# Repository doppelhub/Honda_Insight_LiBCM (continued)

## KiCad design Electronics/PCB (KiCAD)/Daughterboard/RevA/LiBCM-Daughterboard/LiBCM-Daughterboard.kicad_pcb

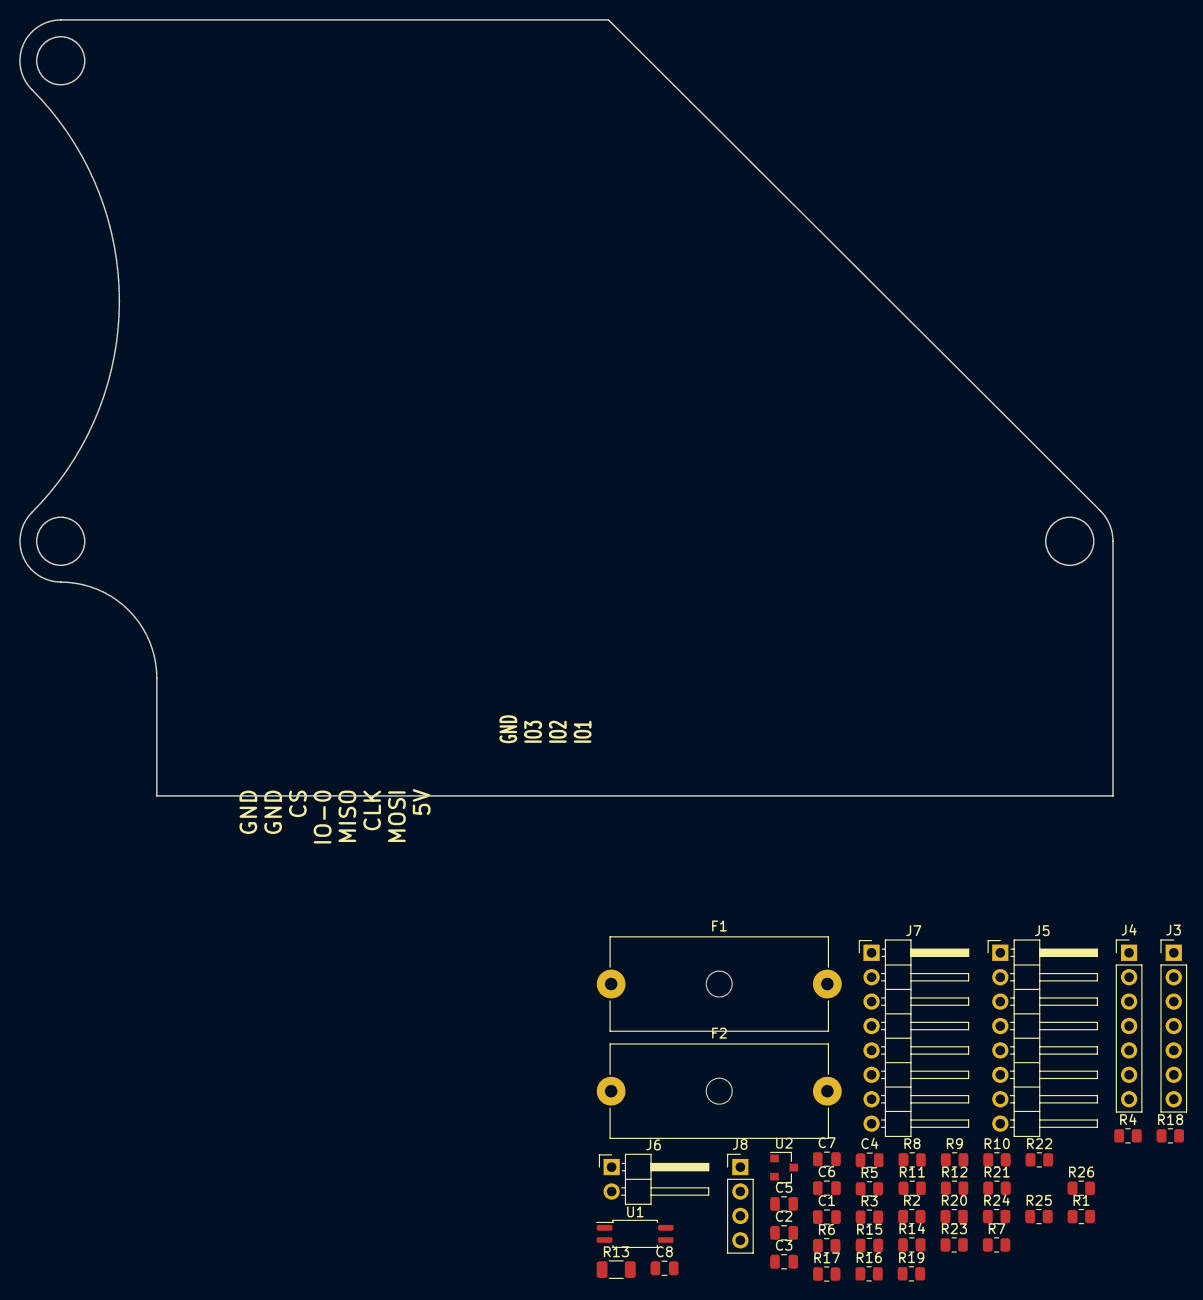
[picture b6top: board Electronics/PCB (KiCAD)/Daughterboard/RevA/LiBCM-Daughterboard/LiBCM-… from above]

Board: 4 copper layers, 113.7 x 80.8 mm, 44 parts (0 on the bottom side), 22 nets, no tracks yet.

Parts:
C1, C2, C3, C4, C5, C7, C8: 100n; C_0805_2012Metric
C6: 1u; C_0805_2012Metric
F1, F2: Fuse; Fuseholder_Cylinder-5x20mm_Schurter_0031_8201_Horizontal_Op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
J3, J4: Conn_01x07; PinHeader_1x07_P2.54mm_Vertical
J5, J7: Conn_01x08; PinHeader_1x08_P2.54mm_Horizontal
J6: Conn_01x02; PinHeader_1x02_P2.54mm_Horizontal
J8: Conn_01x04; PinHeader_1x04_P2.54mm_Vertical
R1, R2, R3, R4: 7k32; R_0805_2012Metric
R5, R6, R7, R18, R24: 10k; R_0805_2012Metric
R8, R9, R23, R25: 768; R_0805_2012Metric
R10, R12: 100; R_0805_2012Metric
R11: 20; R_0805_2012Metric
R13: 5M1; R_1206_3216Metric
R14, R15, R16, R17: 100k; R_0805_2012Metric
R19, R20, R21, R22, R26: DNP; R_0805_2012Metric
U1: APV1121S; SOP-4_4.4x2.6mm_P1.27mm
U2: LM4040DBZ-5; SOT-23

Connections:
+5V: C1.1, C2.1, C3.1, C6.1, J3.1, J4.1, J5.1, J7.1, R1.1, R2.1, R3.1, R4.1
/CHARGER_CURRENT_LIMIT: C8.1, R23.2, R24.1, R25.2, R26.2
/FLASH_CS: J4.7, J5.6, J7.6
/GPIO: J6.1, J8.3, R10.1, R12.1
/GPIO_L1: R10.2, R11.1, R12.2
/GRID_POS_FUSED: F2.1, R14.1, R16.1, R19.1, R21.1
/HVDC_5V_REF: C7.1, R15.2, R17.2, R18.1, R20.2, R22.2, R23.1, R25.1, R26.1, U2.1
/MIMA_CS: J5.5, J7.5
/MISO: J3.4, J4.5, J5.4, J7.4
/MOSI: J3.5, J4.6, J5.3, J7.3
/Q1_GATE: R13.1, U1.4
/SCK: J3.6, J4.4, J5.2, J7.2
/SWITCH__OR__CAN_CS: J3.3, J8.2, R8.2
/TACH_1: R1.2, R5.1
/TACH_2: R2.2, R6.1
/TACH_3: R3.2, R7.1
/TACH_SUM: C5.1, R5.2, R6.2, R7.2, R9.1
/TACH__OR__CAN_INT: J3.7, J8.1, R9.2
/USER_SWITCH: C4.1, R4.2, R8.1
GND: C1.2, C2.2, C3.2, C4.2, C5.2, C6.2, J3.2, J4.3, J5.7, J5.8, J6.2, J7.7, J7.8, J8.4, U1.2
GNDPWR: C7.2, C8.2, R13.2, R18.2, R24.2, U1.3, U2.2
unnamed: R14.2, R15.1, R16.2, R17.1, R19.2, R20.1, R21.2, R22.1

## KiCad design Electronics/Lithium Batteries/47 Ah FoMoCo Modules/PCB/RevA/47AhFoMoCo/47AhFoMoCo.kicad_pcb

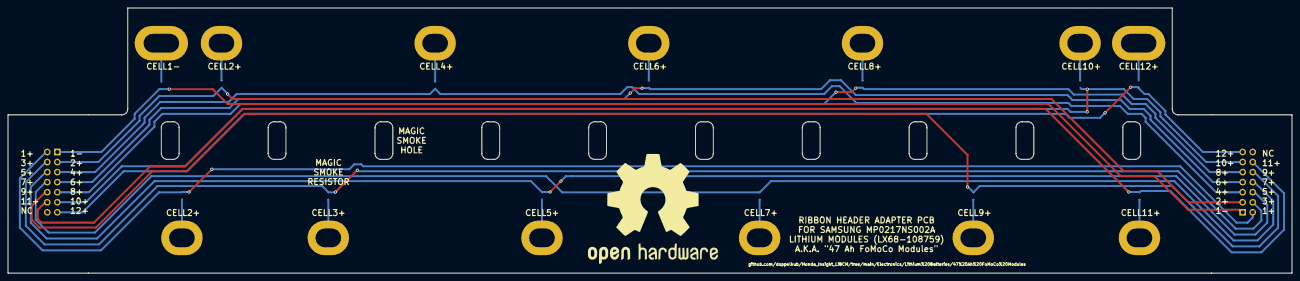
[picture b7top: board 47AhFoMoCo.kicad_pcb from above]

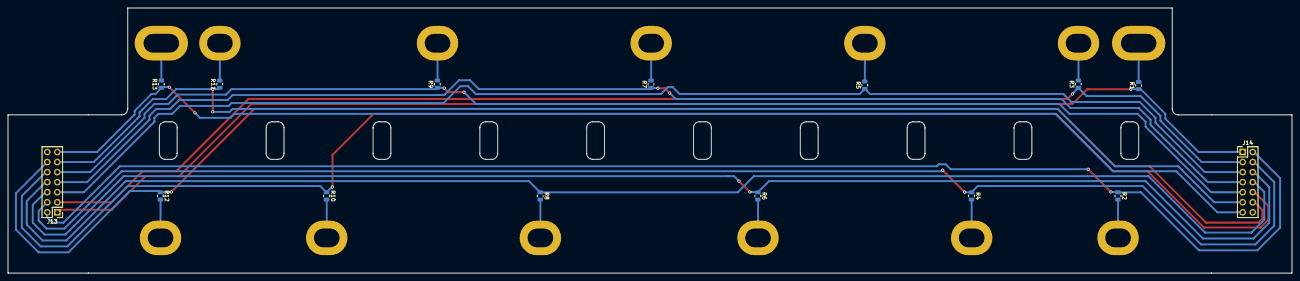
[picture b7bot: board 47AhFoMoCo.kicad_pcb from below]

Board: 2 copper layers, 324.5 x 67.0 mm, 28 parts (15 on the bottom side), 26 nets.

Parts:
J1n1, J12p1: Conn_01x01; BMS Hole_Wide
J1p1, J2p1, J3p1, J4p1, J5p1, J6p1, J7p1, J8p1, J9p1, J10p1, J11p1: Conn_01x01; BMS Hole
J13, J14: Conn_02x07_Odd_Even; PinHeader_2x07_P2.54mm_Vertical
R1, R2, R3, R4, R5, R6, R7, R8, R9, R10, R11, R12, R13: 20; R_0805_2012Metric

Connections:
/CELL01n: J1n1.1, R1.2
/CELL01n_CONN: J13.1, J14.1, R1.1
/CELL01p: J1p1.1, R2.2
/CELL01p_CONN: J13.2, J14.2, R2.1
/CELL02p: J2p1.1, R3.2
/CELL02p_CONN: J13.3, J14.3, R3.1
/CELL03p: J3p1.1, R4.2
/CELL03p_CONN: J13.4, J14.4, R4.1
/CELL04p: J4p1.1, R5.2
/CELL04p_CONN: J13.5, J14.5, R5.1
/CELL05p: J5p1.1, R6.2
/CELL05p_CONN: J13.6, J14.6, R6.1
/CELL06p: J6p1.1, R7.2
/CELL06p_CONN: J13.7, J14.7, R7.1
/CELL07p: J7p1.1, R8.2
/CELL07p_CONN: J13.8, J14.8, R8.1
/CELL08p: J8p1.1, R9.2
/CELL08p_CONN: J13.9, J14.9, R9.1
/CELL09p: J9p1.1, R10.2
/CELL09p_CONN: J13.10, J14.10, R10.1
/CELL10p: J10p1.1, R11.2
/CELL10p_CONN: J13.11, J14.11, R11.1
/CELL11p: J11p1.1, R12.2
/CELL11p_CONN: J13.12, J14.12, R12.1
/CELL12p: J12p1.1, R13.2
/CELL12p_CONN: J13.13, J14.13, R13.1

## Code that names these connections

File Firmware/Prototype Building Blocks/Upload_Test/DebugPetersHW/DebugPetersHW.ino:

//MVP PoC:

/*
* Don't care about:
* -SoC (accumulation)
* -Temperature
* -Fan speed
* -Spoofing ConnE
* -Spoofing Vpin
* -Grid charger
*/

//JTS2do: Move pindefs to a separate header file
#define HW_REVB

#ifdef HW_REVB
  #define PIN_BATTCURRENT A0
  #define PIN_FANOEM_LOW A1
  #define PIN_FANOEM_HI A2
  #define PIN_TEMP_YEL A3
  #define PIN_TEMP_GRN A4
  #define PIN_TEMP_WHT A5
  #define PIN_TEMP_BLU A6
  #define PIN_VPIN_IN A7
  #define PIN_TURNOFFLiBCM A8
  #define PIN_HMI_EN A9
  #define PIN_BATTSCI_DE A10
  #define PIN_BATTSCI_REn A11
  #define PIN_LED1 A12
  #define PIN_LED2 A13
  #define PIN_LED3 A14
  #define PIN_LED4 A15
  
  #define PIN_METSCI_DE 2
  #define PIN_METSCI_REn 3
  #define PIN_VPIN_OUT_PWM 4
  #define PIN_SPI_EXT_CS 5 
  #define PIN_TEMP_EN 6
  #define PIN_CONNE_PWM 7
  #define PIN_GRID_PWM 8
  #define PIN_GRID_SENSE 9
  #define PIN_GRID_EN 10
  #define PIN_FAN_PWM 11
  #define PIN_I_SENSOR_EN 12
  #define PIN_KEY_ON 13
  #define PIN_SPI_CS SS
  #define PIN_GPIO1 48
  #define PIN_USER_SW 49
  
  //Serial3
  #define METSCI_TX 14
  #define METSCI_RX 15
  
  //Serial2
  #define BATTSCI_TX 16
  #define BATTSCI_RX 17
  
  //Serial1
  #define HMI_TX 18
  #define HMI_RX 19
  
  #define DEBUG_SDA 20
  #define DEBUG_CLK 21
#endif

#include <Arduino.h>
#include <stdint.h>
#include "LT_SPI.h"
#include <SPI.h>
#include "LTC68042.h"

struct packetTypes
{
  uint8_t latestE6Packet_assistLevel;
  uint8_t latestB4Packet_engine;
  uint8_t latestB3Packet_engine;
  uint8_t latestE1Packet_SoC;
} METSCI_Packets;

void setup()
{
	//Prevent LiBCM from turning off the 12V->5V DCDC
	pinMode(PIN_TURNOFFLiBCM,OUTPUT);
	digitalWrite(PIN_TURNOFFLiBCM,LOW);
 
	pinMode(PIN_I_SENSOR_EN,OUTPUT);
	digitalWrite(PIN_I_SENSOR_EN,LOW);

	pinMode(PIN_LED1,OUTPUT);
	digitalWrite(PIN_LED1,HIGH);
	pinMode(PIN_LED2,OUTPUT);
	pinMode(PIN_LED3,OUTPUT);
	pinMode(PIN_LED4,OUTPUT);

	pinMode(PIN_CONNE_PWM,OUTPUT);
  analogWrite(PIN_CONNE_PWM,0);
	pinMode(PIN_FAN_PWM,OUTPUT);
	pinMode(PIN_FANOEM_LOW,OUTPUT);
	pinMode(PIN_FANOEM_HI,OUTPUT);
	pinMode(PIN_GRID_EN,OUTPUT);
	pinMode(PIN_VPIN_OUT_PWM,OUTPUT);
  Serial.print("\nPins Set");

  pinMode(PIN_HMI_EN,OUTPUT);
  digitalWrite(PIN_HMI_EN,HIGH); //turn on 4x20 display
  delay(10); //wait for 4x20 to turn on
  Serial.print("\nPass: IO Config");

	analogReference(EXTERNAL); //use 5V AREF pin, which is coupled to filtered VCC

	Serial.begin(115200);	//USB
  Serial.print("\nPass: USB init"); delay(100);
  METSCI_begin();
  Serial.print("\nPass: METSCI init"); delay(100);
  BATTSCI_begin();
  Serial.print("\nPass: BATTSCI init"); delay(100);
  Serial.print("\nPass: one second delay"); delay(1000);
  
  LTC6804_initialize();
  Serial.print("\nPass: LTC6804 init"); delay(100);

  TCCR1B = (TCCR1B & B11111000) | B00000001; // Set onboard fan PWM frequency to 31372 Hz (pins D11 & D12)
  Serial.print("\nPass: set D11/D12 PWM frequency"); delay(100);
    
	Serial.print(F("\n\nPeter's LiBCM HW Debug 2021JUL28a\n\n")); delay(100);
}

//////////////////////////////////////////////////////////////////////////////////////////////////////////////////////////

void loop()
{  
  //Get key position status
  uint8_t keyStatus_now = digitalRead(PIN_KEY_ON);
  static uint8_t keyStatus_previous;
  Serial.print("\nPass(): Key is "); delay(100);
  if(keyStatus_now)
  {
    Serial.print("ON"); delay(100);
  } else {
    Serial.print("OFF"); delay(100);
  }

  //steps to perform when key state changes (on->off, off->on)
  if( keyStatus_now != keyStatus_previous)
  {
    Serial.print(F("\nKey is: ")); delay(100);
    LTC6804_isoSPI_errorCountReset();

    if( keyStatus_now == 0 )
    {
      Serial.print(F("OFF"));
      BATTSCI_disable(); //Must disable BATTSCI when key is off to prevent backdriving MCM
      METSCI_disable();
      digitalWrite(PIN_FANOEM_LOW,LOW);
      digitalWrite(PIN_I_SENSOR_EN,LOW); //disable current sensor & constant 5V load
    } else {
      Serial.print(F("ON"));
      BATTSCI_enable();
      METSCI_enable();
      digitalWrite(PIN_FANOEM_LOW,HIGH);
      digitalWrite(PIN_I_SENSOR_EN,HIGH); //enable current sensor & constant 5V load
    } 
  }
  keyStatus_previous = keyStatus_now;
  
  //---------------------------------------------------------------------------------------

  //Determine whether grid charger is plugged in
  uint8_t gridChargerPowered_now = !(digitalRead(PIN_GRID_SENSE));
  static uint8_t gridChargerPowered_previous;

  //steps to perform when grid charger state changes (plugged in || unplugged)
  if( gridChargerPowered_now != gridChargerPowered_previous)
  {
    Serial.print(F("\nGrid Charger: "));
    if( gridChargerPowered_now == 0 ) //grid charger was just unplugged
    {
      Serial.print(F("Unplugged"));
      analogWrite(PIN_FAN_PWM,0);     //turn onboard fans off
      digitalWrite(PIN_GRID_EN,0);    //turn grid charger off
      Serial.print("\nGrid Charger Disabled");

    } else {                          //grid charger was just plugged in
      Serial.print(F("Plugged In"));
    } 
  }
  gridChargerPowered_previous = gridChargerPowered_now;

  //---------------------------------------------------------------------------------------

  if( (keyStatus_now == 1) || (gridChargerPowered_now == 1) ) //key is on or grid charger plugged in
  {
    digitalWrite(PIN_LED4,HIGH);
    
    LTC6804_startCellVoltageConversion();
    //We don't immediately read the results afterwards because it takes a second to digitize
    //In Coop Task setting we'll need to invoke reading n microseconds after this function is called
    Serial.print("\nPass: LTC6804 Conversion Started"); delay(100);
  
    //---------------------------------------------------------------------------------------

  	//get 64x oversampled current sensor value
    uint16_t ADC_oversampledAccumulator = 0;
    for(int ii=0; ii<64; ii++)  //This takes ~112 us per run (7.2 ms total)
    { 
      ADC_oversampledAccumulator += analogRead(PIN_BATTCURRENT);
    }
    Serial.print("\nPass: Current Sampled"); delay(100);
    
    int16_t ADC_oversampledResult = int16_t( (ADC_oversampledAccumulator >> 6) );
    Serial.print(F("\n\nRaw ADC result is: "));
    Serial.print( String(ADC_oversampledResult) );  
    
  	//convert current sensor result into approximate amperage for MCM & user-display
    //don't use this result for current accumulation... it's not accurate enough
  	int16_t battCurrent_amps = ( (ADC_oversampledResult * 13) >> 6) - 67; //Accurate to within 3.7 amps of actual value
  	Serial.print(F(" counts, which is: "));
    Serial.print( String(battCurrent_amps) );
    Serial.print(F(" amps.  Telling MCM current is: "));
    
    battCurrent_amps = (int16_t)(battCurrent_amps * 0.7); //140% current output required telling MCM 70% of current value
    Serial.print( String(battCurrent_amps) );


    //---------------------------------------------------------------------------------------

  	LTC6804_getCellVoltages(); //individual cell results stored in 'cell_codes' array 
  	
    //sum all 48 cells
  	uint8_t stackVoltage = LTC6804_getStackVoltage();

    //---------------------------------------------------------------------------------------

    if( keyStatus_now ) //key is on
    {
    	//METSCI Decoding
      METSCI_Packets = METSCI_getLatestFrame();
      Serial.print("\nMETSCI E6: " + String(METSCI_Packets.latestE6Packet_assistLevel,HEX) +
                          ", B3: " + String(METSCI_Packets.latestB3Packet_engine,HEX) +
                          ", B4: " + String(METSCI_Packets.latestB4Packet_engine,HEX) +
                          ", E1: " + String(METSCI_Packets.latestE1Packet_SoC,HEX) );

      //---------------------------------------------------------------------------------------  
    	
    	//Send BATTSCI packets to MCM
    	//Need to limit how often this occurs
      BATTSCI_sendFrames(METSCI_Packets, stackVoltage, battCurrent_amps);
    }
    
    delay(100); //forcing buffers to overqueue to verify LiBCM responds correctly
  } else {
    //key is off & grid charger unplugged
    static uint16_t toggleTimer = 0;
    if( ++toggleTimer >= 10000 )
    {
      digitalWrite(PIN_LED4, !digitalRead(PIN_LED4)); //Toggle LED4 (heartbeat)
      toggleTimer=0;   
    }
  }
}

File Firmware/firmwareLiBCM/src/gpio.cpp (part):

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    pinMode(PIN_TURNOFFLiBCM,OUTPUT);
    digitalWrite(PIN_TURNOFFLiBCM,LOW);

    pinMode(PIN_HMI_EN,OUTPUT);
    pinMode(PIN_SENSOR_EN,OUTPUT);
    pinMode(PIN_LED1,OUTPUT);
    pinMode(PIN_LED2,OUTPUT);
    pinMode(PIN_LED3,OUTPUT);
    pinMode(PIN_LED4,OUTPUT);
    analogWrite(PIN_MCME_PWM,0);
    pinMode(PIN_FAN_PWM,OUTPUT);
    pinMode(PIN_FANOEM_LOW,OUTPUT);
    pinMode(PIN_FANOEM_HI,OUTPUT);
    gpio_configureGridChargerPins(); //requires grid charger type, which eeprom_applyBootCriticalConfigOverrides() (called before gpio_begin()) has already resolved
    pinMode(PIN_TEMP_EN,OUTPUT);
    pinMode(PIN_SPI_EXT_CS,OUTPUT);
    digitalWrite(PIN_SPI_EXT_CS,HIGH);

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
//1500W chargers are controlled by a daughterboard, which uses a different pinout than other chargers.
//Grid charger type is a runtime EEPROM value (see eepromAccess.h), so these choose the correct pin at runtime.
uint8_t gpio_pinGridCurrent(void) { return (eeprom_gridChargerType_get() == GRIDCHARGER_TYPE_1500W) ? PIN_GPIO3   : PIN_GRID_PWM; }
uint8_t gpio_pinGridEn(void)      { return (eeprom_gridChargerType_get() == GRIDCHARGER_TYPE_1500W) ? PIN_GRID_PWM : PIN_GRID_EN; }
uint8_t gpio_pinGridVoltage(void) { return PIN_GPIO2; } //only meaningful when grid charger type is 1500W -- other charger types don't support voltage control

void gpio_configureGridChargerPins(void) { pinMode(gpio_pinGridEn(), OUTPUT); }

/////////////////////////////////////////////////////////////////////////////////////////

bool gpio_keyStateNow(void) { return digitalRead(PIN_IGNITION_SENSE); }

/////////////////////////////////////////////////////////////////////////////////////////

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        default: Serial.print(F("\nError: Invalid fan speed"));
    }

    if (fanPWM == 0) { pinMode(PIN_FAN_PWM, INPUT); } //saves power when fan is off
    else             { analogWrite(PIN_FAN_PWM, fanPWM); }
}

/////////////////////////////////////////////////////////////////////////////////////////

//powers OEM current sensor, METSCI/BATTSCI power rail, and constant 5V load
void gpio_turnPowerSensors_on( void) { digitalWrite(PIN_SENSOR_EN, HIGH); }
void gpio_turnPowerSensors_off(void) { digitalWrite(PIN_SENSOR_EN,  LOW); }

/////////////////////////////////////////////////////////////////////////////////////////

void gpio_turnHMI_on( void) { digitalWrite(PIN_HMI_EN, HIGH); }
void gpio_turnHMI_off(void) { digitalWrite(PIN_HMI_EN,  LOW); }
bool gpio_HMIStateNow(void) { return digitalRead(PIN_HMI_EN); }

/////////////////////////////////////////////////////////////////////////////////////////

bool gpio_isGridChargerPluggedInNow(void) { return !(digitalRead(PIN_GRID_SENSE)  ); }
bool gpio_isGridChargerChargingNow(void)  { return   digitalRead(gpio_pinGridEn()); }

/////////////////////////////////////////////////////////////////////////////////////////
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//Buzzer present in RevC+ hardware
void gpio_turnBuzzer_on_highFreq(void)
{
    TCCR5B = (TCCR5B & B11111000) | B00000010; // set F_PWM to  3921.16 Hz //pins D44(GPIO3) & D45(BUZZER) & D46()
    analogWrite(PIN_BUZZER_PWM, 127 );
}

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
void gpio_turnBuzzer_on_lowFreq(void)
{
    TCCR5B = (TCCR5B & B11111000) | B00000011; // set F_PWM to   490.20 Hz //pins D44(GPIO3) & D45(BUZZER) & D46()
    analogWrite(PIN_BUZZER_PWM, 127 );
}

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bool gpio_isCoverInstalled(void)
{
    #ifdef CHECK_FOR_SAFETY_COVER
        if (digitalRead(PIN_COVER_SWITCH) == 1 ) {return  true;}
        else                                     {return false;}
    #else
        return true;
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
/////////////////////////////////////////////////////////////////////////////////////////

bool gpio_isUserSwitchOn(void) { return digitalRead(PIN_USER_SW); }

/////////////////////////////////////////////////////////////////////////////////////////

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
/////////////////////////////////////////////////////////////////////////////////////////

void gpio_turnTemperatureSensors_on( void) {digitalWrite(PIN_TEMP_EN,HIGH); }
void gpio_turnTemperatureSensors_off(void) {digitalWrite(PIN_TEMP_EN, LOW); }

/////////////////////////////////////////////////////////////////////////////////////////

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
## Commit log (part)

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2022-08-06 changed constant names
2022-08-06 fix merge conflicts
2022-08-11 LiDisplay - Fix Grid Charge Page
2022-08-14 Added extra checks for grid charger screen.
2022-08-23 Added more functionality to LiDisplay
2022-08-23 Changed tempSensorFault constant
2022-08-25 Added 47Ah FoMoCo SoC<->VoC LUT
    LiBCM now supports two lithium chemistries!
2022-08-29 47Ah Tray and VoC->SoC Results
2022-09-04 Cleaned up cell balancing logic
2022-09-05 Removed keyOFF SoC delay... balancing now starts immediately on keyOFF
2022-09-05 Added VPIN/MCMe/BATTSCI empirical data
2022-09-07 VPIN_OUT troubleshooting
2022-09-07 Fixed MCM-related VPIN underflow issue
2022-09-12 Increase drive screen element refresh rate.
2022-09-19 Long Term 47Ah FoMoCo VoC->SoC test results
2022-10-04 Pack Discharger
2022-11-14 temp
2022-11-22 38400 Baud Rate
2022-11-28 Prevent 60S P1440 During heavy assist in 3rd/4th/5th gear
    MCM gets upset when output current is too high (due to spoofed voltage). Probably a better way to fix this.
2022-11-28 Added TODO items
2022-12-01 PCB File Structure changed
    Now that LiBCM has multiple PCBs, added a new directory for "motherboard" and "daughterboard"
2022-12-08 Flipped LED
2022-12-09 RevB Heater PCBs, Daughterboard Schematic
2022-12-28 Heat PCB Centroids
2022-12-31 Rewrote VOLTAGE_SPOOFING_ASSIST_ONLY_VARIABLE
    This is now the default (and recommended) voltage spoofing mode.
2023-01-01 Removed MCMe/VPIN debugging code
2023-01-05 Bom Updates
2023-01-06 test code interface changes
2023-01-25 New logic: heater, grid charger, temperature, fans
2023-01-29 Bug fix: Balancing allowed when grid charger plugged in
2023-01-30 Added 4x20 lcdState_handler()
    New architecture removes blocking delay() functions.
2023-02-01 Static LCD text displayed after keyON
2023-02-09 joeaax1j Fan Debug
2023-02-09 cleanup
2023-02-12 Daughterboard Almost Done
2023-02-13 v0.8.6 ready for main
2023-02-27 Add PR gate for passing builds
2023-03-26 Updated Bringup Tester and Daughterboard CARs
2023-04-09 Reduced hasEnoughTimePassedToChangeFanSpeed() sketch size by 32 bytes
2023-04-09 Removed mallocs/frees from LTC68042cell/configure
2023-04-10 Added a buzzer_handler() to service requests from multiple subsystems
2023-04-17 Manual VREF2 test ('$TESTR')
    Verify LTC6802 VREF1 is in bounds.
2023-04-22 Changed Boolean logic to explicit compare
2023-04-22 1500 Watt Charger Support
2023-05-20 RevB Daughterboard
2023-06-08 Notes and Debug Data
2023-06-08 set defaults in config.h
2023-06-09 Autodetect which GPIO heater attached to (if any)
2023-06-09 Removed 'HIGH' & 'LOW' values in analogWrite()
2023-06-09 heater location debug text
2023-06-13 Documented HW Issues
2023-06-30 Daughterboard: V2 RevB BOM, Pick&Place File
2023-07-10 Grid charger bringup tester
2023-07-10 Update grid charger tester values
2023-07-13 Fixed SPI Flash_CS conflict
2023-08-06 TODO notes
2023-08-25 cleaned up $TEST_ code
2023-08-28 $TEST prints deciAmps
2023-08-30 power & current gain user-selectable sign
2023-08-31 MIN_SPOOFED_VOLTAGE_60S to config.h
2023-09-01 more user guardrails
2023-09-01 __TIME__ TODO
2023-09-02 Added missing #endif
2023-09-23 __TIME__ check
2023-09-23 disable watchdog during EEPROM reset
2023-09-23 Removed debug printf
2023-09-24 added watchdog reset to eeprom erase
2023-09-27 Fix Avg cell vltg display on grid chrg page.
2023-09-28 Fixed date, removed balancing note as it would only work if USB was plugged into a computer.
2023-10-03 Set baud to 57600
2023-10-04 Elapsed time added to driving screen
2023-10-23 Changes to config.
2023-10-24 RevD BOM updates
2023-11-06 Increased I_sense cal limits
2023-12-15 Match @Lady-Natalya's latest FW version
2023-12-15 disabled config.h user config
2023-12-31 TODO: Fan test
2024-01-11 Version
2024-01-12 Update battsci.cpp
    move background regen to more suitable position for lithium
2024-01-19 disable hardware defaults
2024-01-27 Update vPackSpoof.cpp
    maxAllowedVspoof now ramps in from 120v to improve driveability. Cut-in using OEM mode with 48S was previously a rough input from idle speed.
2024-02-05 Update battsci.cpp
    revised LUT to expand battery range from 20-80%SOC (NiMH) to 10-85%SOC (Lithium) but moved other adjustment to curve shape into REDUCE_BACKGROUND_REGEN_UNLESS_BRAKING which now has a progressive cut-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
    The gives improved PHEV operation in OEM mode.
2024-02-19 Updated handling of changes to power state
2024-02-23 Update battsci.cpp
    Look Up Table expands battery range from 20-80%SOC (NiMH) to 10-85%SOC (Lithium). NB Large deviations from 1:1 disabled all brake regen, so this cannot be relied upon to disable background regen.
    therefore regen setpoints now adjusted using background regen conig option.
    Ramped cut in of background charging at low SOC for improved drieability
    //15%SOC Background charge disabled
    //14%SOC Background charge enabled
    //13%SOC Regen during coasting
2024-02-27 Update battsci.cpp
    a large change in SOC from gridcharging meant that the battsci value jumped and missed out key setpoints. (eg grid charge from 15% to 82% and background regen was still enabled)
    with this change previousOutputSoC_deciPercent is set to 65%SOC at key-on, therefore all appropriate setpoints are triggered shortly after keyon. In the above example, SOC 72% would be triggered and 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
    If the pack had decreased since last key on, bg regen would be triggered if below 60%SOC or 15% if bg regen is disabled.
2024-03-03 UHP1500 Fan Control PCB, RevB FoMoCo Mechanicals
2024-03-06 LCD Cell Balancing Flag
2024-03-06 user guard when eeprom_resetAll()
2024-03-07 Update vPackSpoof.cpp
    VOLTAGE_SPOOFING_LINEAR
    spoofedPackVoltage = actualPackVoltage * 0.4 + 72
2024-03-08 Update vPackSpoof.cpp
    -16v
2024-03-08 remove comments
2024-03-10 Remove user fan request when GC or key unplugged/off
2024-03-12 Update battsci.cpp
    key on SOC value now 62%.
    With 65%, grid charge resulted in BG regen from 83% SOC until below 80% SOC
2024-03-13 Update battsci.cpp
    Moved upper band from MCM720 to MCM800 so that important setpoint MCM720 is triggered if key-on SOC is between 75-85%SOC, Above 85% regen should disable (needs to be confirmed)
2024-03-25 deleted coments, added some preparations for cell voltage display while driving
2024-04-01 Fixed bugs on GC page, added Balancing info to GC page, fixed ccell delta on driving page.
2024-04-24 Slowed LCD refresh
2024-05-01 Switch to use new cellBalance_areCellsBalancing() function.
2024-05-08 BATTSCI/METSCI data
2024-05-14 bringup temp go/nogo limits
2024-05-14 removed bringupTester cellQTY check
2024-05-14 Display entire 4x20 FW Install Message
2024-05-29 BOM update
2024-07-11 Graceful Cold Boot
2024-07-11 '$OFF' debug command
2024-07-12 consolidated changes
2024-07-19 Uptime debug
2024-07-23 store isoSPI timestamp when sending data
2024-07-24 Update CAR066 with root cause
2024-07-24 Init LiControl before LTC68042
2024-07-24 Cold Boot Proof of Concept (#58)
    Graceful Cold Boot PoC
2024-08-19 Changed format of LiDisplay_handler loop
2024-08-22 Fix big
    Added uint8_t vspoofMCM_max = calculate_vspoofMCM_max(); to my spoof function.
2024-08-22 Update a constant name and add a comment
    Changed VSPOOF_60S_DISABLE_VOLTAGE to
    DISABLE_60S_VSPOOF_VOLTAGE. Also upped this constant's value from 170 to 177.
2024-08-28 Update vPackSpoof.cpp
    (Possibly) Fix previous terrible code. Idea is to add a minimum spoofed voltage value.
2024-08-31 Switch to use a constant for minimum VSpoof code.
    Update description of Bull Dog's VSPOOF code.
    Added VSPOOF60S_MINIMUM_VOLTAGE constant to vPackSpoof.h
    Changd the minimum VSpoof voltage limiting code to use a constant instead of just "145" Also tweaked formatting to follow existing formatting.
2024-09-05 minor changes
2024-09-05 Modularization of LiDisplay.cpp (#60)
    * Initial Commit
    * Changed format of LiDisplay_handler loop
    * minor changes
    * Added some clarifying comments.
2024-09-27 Final quality check before pull request.
    Updated descriptions for configuring VOLTAGE_SPOOFING_VARIABLE_60S_BULL_DOG in config.h.
    Cleaned up the comments in the VOLTAGE_SPOOFING_VARIABLE_60S_BULL_DOG section of vPackSpoof.cpp
2024-10-08 LiBCM now turns off 5 days after keyOff
    LiBCM turns back on with keyOn, USB power, or toggling IMA switch.
2024-10-08 time cast to uint32_t before multiply
2024-11-01 Increased FW expiration to 120 days
2024-11-11 Added 12A Charger
    * Added my new charger option
    * Added variable charge level (0-100%
    * Added new command to ASM, and the ability to change the set charge level. ($CHGPWR=___ )
    * Added a tapered charge power at the top of SoC
    * Updated terminology for grid charger options
2024-11-16 Fix config file.
2024-11-16 Support for temp display on GC Page.
2024-11-27 cleaned up 4x20 Wh & time code
2024-12-31 (new) energy.c
2025-02-27 First cut at re-mapping 5AhG3 thermistors to FoMoCo battery type.
    This aligns firmware thermistor use with the hardware. For the FoMoCo
    case, this is the thermistor use:
    5AhG3 FoMoCo
    OEM GRN: IMA Intake Top rear battery module
    OEM YEL: IMA Exhaust Top middle battery module
    OEM WHT: Ambient IMA Intake
2025-03-12 Removed double calls of LTC68042cell_nextVoltages().
    Now that LTC68042cell_nextVoltages() waits for an acquisition to
    complete, double calls should not be needed to prevent stale data.
2025-03-15 P&P files, ReadMe, TODO, CARs
2025-03-15 disable fans
2025-03-22 Reworked state machine to add LTC_WAITING_FOR_ADC state
    Also:
    Renamed trigger modes
    Backed out conversionExpectedDuration_us
    Renamed startCellConversion() to better describe what it now does.
    Updated description of LTC68042cell_nextVoltages()
2025-04-01 Fixed DONE__READY_TO_TRIGGER value
2025-04-23 Changed doCellDataGather() to return nextPresentState.
    Via git checkout --patch WGC_SABOTAGEDNoMergeWaitAcqComplete src/LTC68042cell.cpp
2025-04-25 Reverted some style changes for easier PR
2025-05-25 TODO notes & gridCharger Tester
2025-06-06 LiDisplay 2025 - Adding nerd screen option.
2025-06-09 more work on lidisplay
2025-06-18 Wh Trip Feature with Grid Charging
2025-06-18 default config.h options
2025-06-18 debugging page element id even more
2025-06-20 Spoofed value formatting.
2025-06-22 Rewrote processAllCellVoltages()
    Old function was messy due to 5AhG3cell#19 HW hack.
    Fixed trivial bug: Vpack didn't include actual cell#19 voltage.
    Added new functions:
    LTC68042result_hiCellNum_get() LTC68042result_loCellNum_get()
2025-06-22 Revert to production values
2025-06-23 Lowest Cell and Highest Cell IDs display on NS
2025-06-26 Improved Vspoof function names
2025-07-01 'MVO' renamed to 'MDV'
    Peter changed the MCMe OBDIIC&C parameter name years ago.
2025-07-15 ASM now shows hi/lo cell#
2025-07-28 More work on NS page.
2025-08-13 Merged charger code to JTS branch
2025-08-15 Abstract serial communications.
2025-08-15 Command page id fix.
2025-08-15 NS Updates
2025-08-27 Update vPackSpoof.cpp
    New curve for 48S/60S so that peak current is used for both battery installs.
2025-09-18 Fix T22 Error and Fix Screen change errors
2025-09-26 Updates to Settings page
2025-10-16 Grid charging timer no longer uses modulo or division
2025-11-05 Made Requested Changes
2025-12-30 Major LiDisplay Updates - Energy Trip Meter added.
2025-12-30 Settings page trip display updates while driving
2026-01-08 Grid Charger Trip Meter added with litre gas equiv and GGE display
2026-02-21 32 bit int for LiDisplay wh tracking
2026-03-26 uint32_t in energy.h
2026-04-16 Integer Overflow Solved
